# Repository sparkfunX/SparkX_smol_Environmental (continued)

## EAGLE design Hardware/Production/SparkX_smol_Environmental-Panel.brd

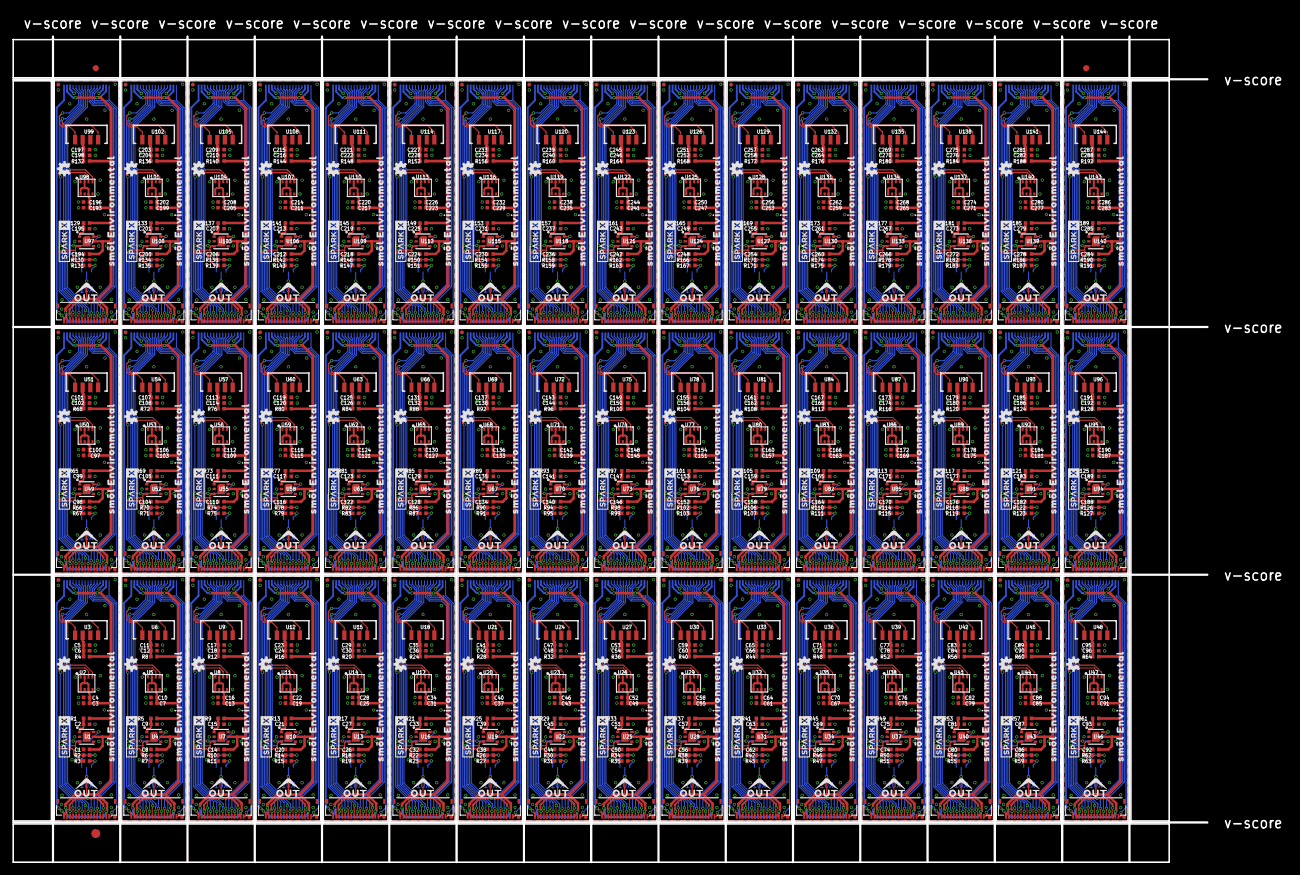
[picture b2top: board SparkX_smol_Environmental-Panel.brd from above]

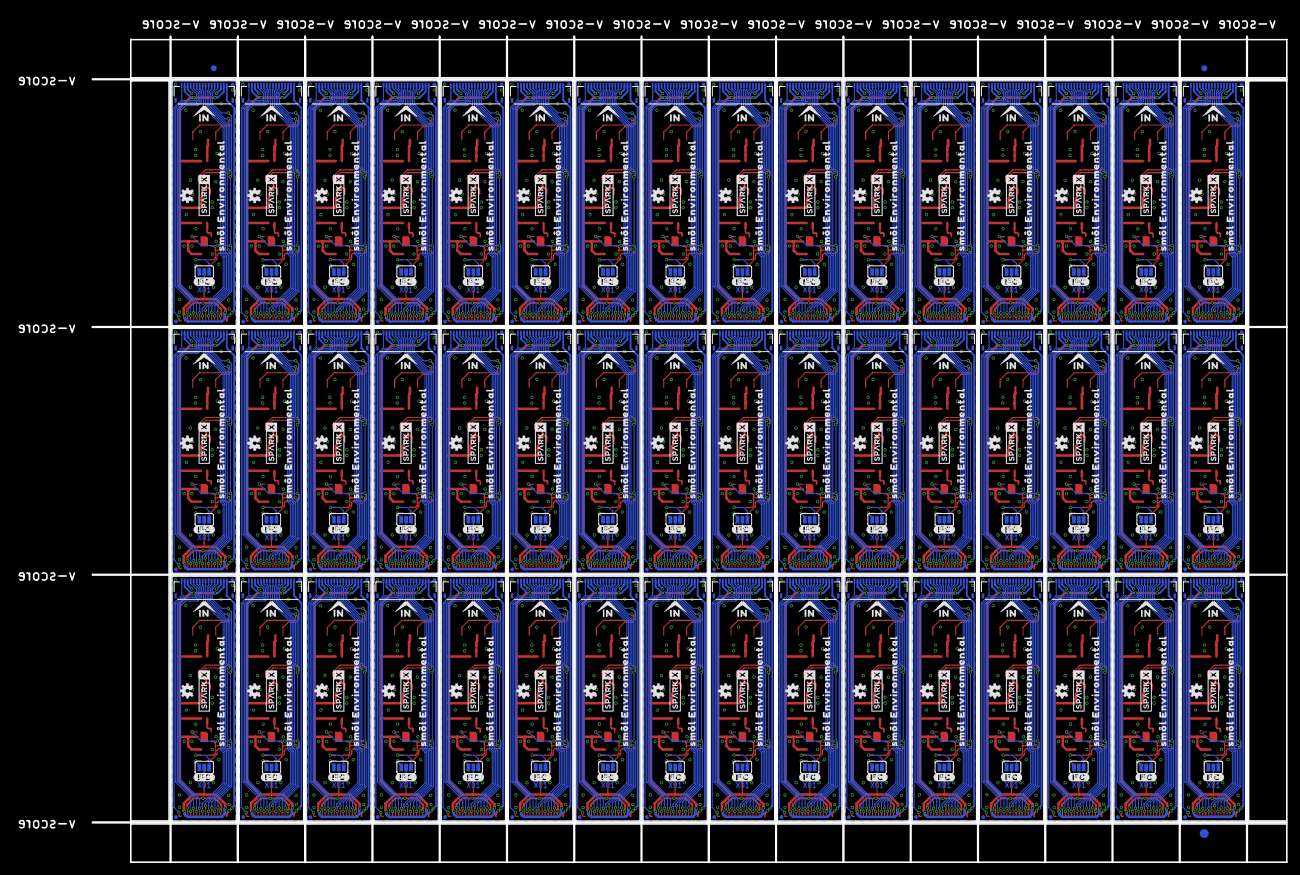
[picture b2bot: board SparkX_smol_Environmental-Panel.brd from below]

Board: 2 copper layers, 198.4 x 137.2 mm, 1494 parts (483 on the bottom side), 864 nets.

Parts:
C1, C2, C8, C9, C14, C15, C20, C21, C26, C27, C32, C33, C38, C39, C44, C45, C50, C51, C56, C57, C62, C63, C68, C69, C74, C75, C80, C81, C86, C87, C92, C93, C98, C99, C104, C105, C110, C111, C116, C117, C122, C123, C128, C129, C134, C135, C140, C141, C146, C147, C152, C153, C158, C159, C164, C165, C170, C171, C176, C177, C182, C183, C188, C189, C194, C195, C200, C201, C206, C207, C212, C213, C218, C219, C224, C225, C230, C231, C236, C237, C242, C243, C248, C249, C254, C255, C260, C261, C266, C267, C272, C273, C278, C279, C284, C285: 1.0uF; 0402-TIGHT
C3, C5, C7, C11, C13, C17, C19, C23, C25, C29, C31, C35, C37, C41, C43, C47, C49, C53, C55, C59, C61, C65, C67, C71, C73, C77, C79, C83, C85, C89, C91, C95, C97, C101, C103, C107, C109, C113, C115, C119, C121, C125, C127, C131, C133, C137, C139, C143, C145, C149, C151, C155, C157, C161, C163, C167, C169, C173, C175, C179, C181, C185, C187, C191, C193, C197, C199, C203, C205, C209, C211, C215, C217, C221, C223, C227, C229, C233, C235, C239, C241, C245, C247, C251, C253, C257, C259, C263, C265, C269, C271, C275, C277, C281, C283, C287: 2.2uF; 0402-TIGHT
C4, C6, C10, C12, C16, C18, C22, C24, C28, C30, C34, C36, C40, C42, C46, C48, C52, C54, C58, C60, C64, C66, C70, C72, C76, C78, C82, C84, C88, C90, C94, C96, C100, C102, C106, C108, C112, C114, C118, C120, C124, C126, C130, C132, C136, C138, C142, C144, C148, C150, C154, C156, C160, C162, C166, C168, C172, C174, C178, C180, C184, C186, C190, C192, C196, C198, C202, C204, C208, C210, C214, C216, C220, C222, C226, C228, C232, C234, C238, C240, C244, C246, C250, C252, C256, C258, C262, C264, C268, C270, C274, C276, C280, C282, C286, C288: 0.1uF; 0402-TIGHT
E$1, E$2, E$3, E$4: FIDUCIAL-1X2
E$5, E$6: FIDUCIAL-1.5X3
FD1, FD2, FD3, FD4, FD5, FD6, FD7, FD8, FD9, FD10, FD11, FD12, FD13, FD14, FD15, FD16, FD17, FD18, FD19, FD20, FD21, FD22, FD23, FD24, FD25, FD26, FD27, FD28, FD29, FD30, FD31, FD32, FD33, FD34, FD35, FD36, FD37, FD38, FD39, FD40, FD41, FD42, FD43, FD44, FD45, FD46, FD47, FD48, FD49, FD50, FD51, FD52, FD53, FD54, FD55, FD56, FD57, FD58, FD59, FD60, FD61, FD62, FD63, FD64, FD65, FD66, FD67, FD68, FD69, FD70, FD71, FD72, FD73, FD74, FD75, FD76, FD77, FD78, FD79, FD80, FD81, FD82, FD83, FD84, FD85, FD86, FD87, FD88, FD89, FD90, FD91, FD92, FD93, FD94, FD95, FD96, FD97, FD98, FD99, FD100, FD101, FD102, FD103, FD104, FD105, FD106, FD107, FD108, FD109, FD110, FD111, FD112, FD113, FD114, FD115, FD116, FD117, FD118, FD119, FD120, FD121, FD122, FD123, FD124, FD125, FD126, FD127, FD128, FD129, FD130, FD131, FD132, FD133, FD134, FD135, FD136, FD137, FD138, FD139, FD140, FD141, FD142, FD143, FD144, FD145, FD146, FD147, FD148, FD149, FD150, FD151, FD152, FD153, FD154, FD155, FD156, FD157, FD158, FD159, FD160, FD161, FD162, FD163, FD164, FD165, FD166, FD167, FD168, FD169, FD170, FD171, FD172, FD173, FD174, FD175, FD176, FD177, FD178, FD179, FD180, FD181, FD182, FD183, FD184, FD185, FD186, FD187, FD188, FD189, FD190, FD191, FD192: FIDUCIALUFIDUCIAL; FIDUCIAL-MICRO
IN, IN1, IN2, IN3, IN4, IN5, IN6, IN7, IN8, IN9, IN10, IN11, IN12, IN13, IN14, IN15, IN16, IN17, IN18, IN19, IN20, IN21, IN22, IN23, IN24, IN25, IN26, IN27, IN28, IN29, IN30, IN31, IN32, IN33, IN34, IN35, IN36, IN37, IN38, IN39, IN40, IN41, IN42, IN43, IN44, IN45, IN46, IN47: FPC_16_0.5MM
JP1, JP2, JP3, JP4, JP5, JP6, JP7, JP8, JP9, JP10, JP11, JP12, JP13, JP14, JP15, JP16, JP17, JP18, JP19, JP20, JP21, JP22, JP23, JP24, JP25, JP26, JP27, JP28, JP29, JP30, JP31, JP32, JP33, JP34, JP35, JP36, JP37, JP38, JP39, JP40, JP41, JP42, JP43, JP44, JP45, JP46, JP47, JP48: JUMPER-SMT_3_NO_SILK; SMT-JUMPER_3_NO_SILK
LOGO1, LOGO2, LOGO3, LOGO4, LOGO5, LOGO6, LOGO7, LOGO8, LOGO9, LOGO10, LOGO11, LOGO12, LOGO13, LOGO14, LOGO15, LOGO16, LOGO17, LOGO18, LOGO19, LOGO20, LOGO21, LOGO22, LOGO23, LOGO24, LOGO25, LOGO26, LOGO27, LOGO28, LOGO29, LOGO30, LOGO31, LOGO32, LOGO33, LOGO34, LOGO35, LOGO36, LOGO37, LOGO38, LOGO39, LOGO40, LOGO41, LOGO42, LOGO43, LOGO44, LOGO45, LOGO46, LOGO47, LOGO48, LOGO49, LOGO50, LOGO51, LOGO52, LOGO53, LOGO54, LOGO55, LOGO56, LOGO57, LOGO58, LOGO59, LOGO60, LOGO61, LOGO62, LOGO63, LOGO64, LOGO65, LOGO66, LOGO67, LOGO68, LOGO69, LOGO70, LOGO71, LOGO72, LOGO73, LOGO74, LOGO75, LOGO76, LOGO77, LOGO78, LOGO79, LOGO80, LOGO81, LOGO82, LOGO83, LOGO84, LOGO85, LOGO86, LOGO87, LOGO88, LOGO89, LOGO90, LOGO91, LOGO92, LOGO93, LOGO94, LOGO95, LOGO96: OSHW-LOGOMINI; OSHW-LOGO-MINI
OUT, OUT1, OUT2, OUT3, OUT4, OUT5, OUT6, OUT7, OUT8, OUT9, OUT10, OUT11, OUT12, OUT13, OUT14, OUT15, OUT16, OUT17, OUT18, OUT19, OUT20, OUT21, OUT22, OUT23, OUT24, OUT25, OUT26, OUT27, OUT28, OUT29, OUT30, OUT31, OUT32, OUT33, OUT34, OUT35, OUT36, OUT37, OUT38, OUT39, OUT40, OUT41, OUT42, OUT43, OUT44, OUT45, OUT46, OUT47: FPC_16_0.5MM
R1, R4, R5, R8, R9, R12, R13, R16, R17, R20, R21, R24, R25, R28, R29, R32, R33, R36, R37, R40, R41, R44, R45, R48, R49, R52, R53, R56, R57, R60, R61, R64, R65, R68, R69, R72, R73, R76, R77, R80, R81, R84, R85, R88, R89, R92, R93, R96, R97, R100, R101, R104, R105, R108, R109, R112, R113, R116, R117, R120, R121, R124, R125, R128, R129, R132, R133, R136, R137, R140, R141, R144, R145, R148, R149, R152, R153, R156, R157, R160, R161, R164, R165, R168, R169, R172, R173, R176, R177, R180, R181, R184, R185, R188, R189, R192: 4.7; 0402-TIGHT
R2, R3, R6, R7, R10, R11, R14, R15, R18, R19, R22, R23, R26, R27, R30, R31, R34, R35, R38, R39, R42, R43, R46, R47, R50, R51, R54, R55, R58, R59, R62, R63, R66, R67, R70, R71, R74, R75, R78, R79, R82, R83, R86, R87, R90, R91, R94, R95, R98, R99, R102, R103, R106, R107, R110, R111, R114, R115, R118, R119, R122, R123, R126, R127, R130, R131, R134, R135, R138, R139, R142, R143, R146, R147, R150, R151, R154, R155, R158, R159, R162, R163, R166, R167, R170, R171, R174, R175, R178, R179, R182, R183, R186, R187, R190, R191: 4.7k; 0402-TIGHT
U1, U4, U7, U10, U13, U16, U19, U22, U25, U28, U31, U34, U37, U40, U43, U46, U49, U52, U55, U58, U61, U64, U67, U70, U73, U76, U79, U82, U85, U88, U91, U94, U97, U100, U103, U106, U109, U112, U115, U118, U121, U124, U127, U130, U133, U136, U139, U142: SGP40
U2, U5, U8, U11, U14, U17, U20, U23, U26, U29, U32, U35, U38, U41, U44, U47, U50, U53, U56, U59, U62, U65, U68, U71, U74, U77, U80, U83, U86, U89, U92, U95, U98, U101, U104, U107, U110, U113, U116, U119, U122, U125, U128, U131, U134, U137, U140, U143: BME280; LGA-8-2.5X2.5
U3, U6, U9, U12, U15, U18, U21, U24, U27, U30, U33, U36, U39, U42, U45, U48, U51, U54, U57, U60, U63, U66, U69, U72, U75, U78, U81, U84, U87, U90, U93, U96, U99, U102, U105, U108, U111, U114, U117, U120, U123, U126, U129, U132, U135, U138, U141, U144: VEML7700-TT; VEML7700_TT
U$1, U$6, U$7, U$18, U$19, U$20, U$28, U$29, U$37, U$38, U$46, U$47, U$55, U$56, U$64, U$65, U$73, U$74, U$82, U$83, U$91, U$92, U$100, U$101, U$109, U$110, U$118, U$119, U$127, U$128, U$136, U$137, U$145, U$146, U$154, U$155, U$163, U$164, U$172, U$173, U$181, U$182, U$190, U$191, U$199, U$200, U$208, U$209, U$217, U$218, U$226, U$227, U$235, U$236, U$244, U$245, U$253, U$254, U$262, U$263, U$271, U$272, U$280, U$281, U$289, U$290, U$298, U$299, U$307, U$308, U$316, U$317, U$325, U$326, U$334, U$335, U$343, U$344, U$352, U$353, U$361, U$362, U$370, U$371, U$379, U$380, U$388, U$389, U$397, U$398, U$406, U$407, U$415, U$416, U$424, U$425: SPARKX-LOGO3; SPARKX-SMALL
U$2, U$4, U$14, U$15, U$25, U$26, U$34, U$35, U$43, U$44, U$52, U$53, U$61, U$62, U$70, U$71, U$79, U$80, U$88, U$89, U$97, U$98, U$106, U$107, U$115, U$116, U$124, U$125, U$133, U$134, U$142, U$143, U$151, U$152, U$160, U$161, U$169, U$170, U$178, U$179, U$187, U$188, U$196, U$197, U$205, U$206, U$214, U$215, U$223, U$224, U$232, U$233, U$241, U$242, U$250, U$251, U$259, U$260, U$268, U$269, U$277, U$278, U$286, U$287, U$295, U$296, U$304, U$305, U$313, U$314, U$322, U$323, U$331, U$332, U$340, U$341, U$349, U$350, U$358, U$359, U$367, U$368, U$376, U$377, U$385, U$386, U$394, U$395, U$403, U$404, U$412, U$413, U$421, U$422, U$430, U$431: SM�L_ENVIRONMENTAL0
U$3, U$9, U$12, U$13, U$23, U$24, U$32, U$33, U$41, U$42, U$50, U$51, U$59, U$60, U$68, U$69, U$77, U$78, U$86, U$87, U$95, U$96, U$104, U$105, U$113, U$114, U$122, U$123, U$131, U$132, U$140, U$141, U$149, U$150, U$158, U$159, U$167, U$168, U$176, U$177, U$185, U$186, U$194, U$195, U$203, U$204, U$212, U$213, U$221, U$222, U$230, U$231, U$239, U$240, U$248, U$249, U$257, U$258, U$266, U$267, U$275, U$276, U$284, U$285, U$293, U$294, U$302, U$303, U$311, U$312, U$320, U$321, U$329, U$330, U$338, U$339, U$347, U$348, U$356, U$357, U$365, U$366, U$374, U$375, U$383, U$384, U$392, U$393, U$401, U$402, U$410, U$411, U$419, U$420, U$428, U$429: SMOL_LOGOSMALL; SMOL_SMALL
U$5, U$16, U$27, U$36, U$45, U$54, U$63, U$72, U$81, U$90, U$99, U$108, U$117, U$126, U$135, U$144, U$153, U$162, U$171, U$180, U$189, U$198, U$207, U$216, U$225, U$234, U$243, U$252, U$261, U$270, U$279, U$288, U$297, U$306, U$315, U$324, U$333, U$342, U$351, U$360, U$369, U$378, U$387, U$396, U$405, U$414, U$423, U$432: #I�C#0
U$8, U$10, U$21, U$30, U$39, U$48, U$57, U$66, U$75, U$84, U$93, U$102, U$111, U$120, U$129, U$138, U$147, U$156, U$165, U$174, U$183, U$192, U$201, U$210, U$219, U$228, U$237, U$246, U$255, U$264, U$273, U$282, U$291, U$300, U$309, U$318, U$327, U$336, U$345, U$354, U$363, U$372, U$381, U$390, U$399, U$408, U$417, U$426: IN0
U$11, U$17, U$22, U$31, U$40, U$49, U$58, U$67, U$76, U$85, U$94, U$103, U$112, U$121, U$130, U$139, U$148, U$157, U$166, U$175, U$184, U$193, U$202, U$211, U$220, U$229, U$238, U$247, U$256, U$265, U$274, U$283, U$292, U$301, U$310, U$319, U$328, U$337, U$346, U$355, U$364, U$373, U$382, U$391, U$400, U$409, U$418, U$427: OUT0

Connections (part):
3.3V: C1.1, C3.1, C4.1, IN.2, IN.15, JP1.2, OUT.2, OUT.15, R1.2, R4.2, U1.5, U2.2, U2.6, U2.8
3.3V1: C7.1, C8.1, C10.1, IN1.2, IN1.15, JP2.2, OUT1.2, OUT1.15, R5.2, R8.2, U4.5, U5.2, U5.6, U5.8
3.3V2: C13.1, C14.1, C16.1, IN2.2, IN2.15, JP3.2, OUT2.2, OUT2.15, R9.2, R12.2, U7.5, U8.2, U8.6, U8.8
3.3V3: C19.1, C20.1, C22.1, IN3.2, IN3.15, JP4.2, OUT3.2, OUT3.15, R13.2, R16.2, U10.5, U11.2, U11.6, U11.8
3.3V4: C25.1, C26.1, C28.1, IN4.2, IN4.15, JP5.2, OUT4.2, OUT4.15, R17.2, R20.2, U13.5, U14.2, U14.6, U14.8
3.3V5: C31.1, C32.1, C34.1, IN5.2, IN5.15, JP6.2, OUT5.2, OUT5.15, R21.2, R24.2, U16.5, U17.2, U17.6, U17.8
3.3V6: C37.1, C38.1, C40.1, IN6.2, IN6.15, JP7.2, OUT6.2, OUT6.15, R25.2, R28.2, U19.5, U20.2, U20.6, U20.8
3.3V7: C43.1, C44.1, C46.1, IN7.2, IN7.15, JP8.2, OUT7.2, OUT7.15, R29.2, R32.2, U22.5, U23.2, U23.6, U23.8
3.3V8: C49.1, C50.1, C52.1, IN8.2, IN8.15, JP9.2, OUT8.2, OUT8.15, R33.2, R36.2, U25.5, U26.2, U26.6, U26.8
3.3V9: C55.1, C56.1, C58.1, IN9.2, IN9.15, JP10.2, OUT9.2, OUT9.15, R37.2, R40.2, U28.5, U29.2, U29.6, U29.8
3.3V10: C61.1, C62.1, C64.1, IN10.2, IN10.15, JP11.2, OUT10.2, OUT10.15, R41.2, R44.2, U31.5, U32.2, U32.6, U32.8
3.3V11: C67.1, C68.1, C70.1, IN11.2, IN11.15, JP12.2, OUT11.2, OUT11.15, R45.2, R48.2, U34.5, U35.2, U35.6, U35.8
3.3V12: C73.1, C74.1, C76.1, IN12.2, IN12.15, JP13.2, OUT12.2, OUT12.15, R49.2, R52.2, U37.5, U38.2, U38.6, U38.8
3.3V13: C79.1, C80.1, C82.1, IN13.2, IN13.15, JP14.2, OUT13.2, OUT13.15, R53.2, R56.2, U40.5, U41.2, U41.6, U41.8
3.3V14: C85.1, C86.1, C88.1, IN14.2, IN14.15, JP15.2, OUT14.2, OUT14.15, R57.2, R60.2, U43.5, U44.2, U44.6, U44.8
3.3V15: C91.1, C92.1, C94.1, IN15.2, IN15.15, JP16.2, OUT15.2, OUT15.15, R61.2, R64.2, U46.5, U47.2, U47.6, U47.8
3.3V16: C97.1, C98.1, C100.1, IN16.2, IN16.15, JP17.2, OUT16.2, OUT16.15, R65.2, R68.2, U49.5, U50.2, U50.6, U50.8
3.3V17: C103.1, C104.1, C106.1, IN17.2, IN17.15, JP18.2, OUT17.2, OUT17.15, R69.2, R72.2, U52.5, U53.2, U53.6, U53.8
3.3V18: C109.1, C110.1, C112.1, IN18.2, IN18.15, JP19.2, OUT18.2, OUT18.15, R73.2, R76.2, U55.5, U56.2, U56.6, U56.8
3.3V19: C115.1, C116.1, C118.1, IN19.2, IN19.15, JP20.2, OUT19.2, OUT19.15, R77.2, R80.2, U58.5, U59.2, U59.6, U59.8
3.3V20: C121.1, C122.1, C124.1, IN20.2, IN20.15, JP21.2, OUT20.2, OUT20.15, R81.2, R84.2, U61.5, U62.2, U62.6, U62.8
3.3V21: C127.1, C128.1, C130.1, IN21.2, IN21.15, JP22.2, OUT21.2, OUT21.15, R85.2, R88.2, U64.5, U65.2, U65.6, U65.8
3.3V22: C133.1, C134.1, C136.1, IN22.2, IN22.15, JP23.2, OUT22.2, OUT22.15, R89.2, R92.2, U67.5, U68.2, U68.6, U68.8
3.3V23: C139.1, C140.1, C142.1, IN23.2, IN23.15, JP24.2, OUT23.2, OUT23.15, R93.2, R96.2, U70.5, U71.2, U71.6, U71.8
3.3V24: C145.1, C146.1, C148.1, IN24.2, IN24.15, JP25.2, OUT24.2, OUT24.15, R97.2, R100.2, U73.5, U74.2, U74.6, U74.8
3.3V25: C151.1, C152.1, C154.1, IN25.2, IN25.15, JP26.2, OUT25.2, OUT25.15, R101.2, R104.2, U76.5, U77.2, U77.6, U77.8
3.3V26: C157.1, C158.1, C160.1, IN26.2, IN26.15, JP27.2, OUT26.2, OUT26.15, R105.2, R108.2, U79.5, U80.2, U80.6, U80.8
3.3V27: C163.1, C164.1, C166.1, IN27.2, IN27.15, JP28.2, OUT27.2, OUT27.15, R109.2, R112.2, U82.5, U83.2, U83.6, U83.8
3.3V28: C169.1, C170.1, C172.1, IN28.2, IN28.15, JP29.2, OUT28.2, OUT28.15, R113.2, R116.2, U85.5, U86.2, U86.6, U86.8
3.3V29: C175.1, C176.1, C178.1, IN29.2, IN29.15, JP30.2, OUT29.2, OUT29.15, R117.2, R120.2, U88.5, U89.2, U89.6, U89.8
3.3V30: C181.1, C182.1, C184.1, IN30.2, IN30.15, JP31.2, OUT30.2, OUT30.15, R121.2, R124.2, U91.5, U92.2, U92.6, U92.8
3.3V31: C187.1, C188.1, C190.1, IN31.2, IN31.15, JP32.2, OUT31.2, OUT31.15, R125.2, R128.2, U94.5, U95.2, U95.6, U95.8
3.3V32: C193.1, C194.1, C196.1, IN32.2, IN32.15, JP33.2, OUT32.2, OUT32.15, R129.2, R132.2, U97.5, U98.2, U98.6, U98.8
3.3V33: C199.1, C200.1, C202.1, IN33.2, IN33.15, JP34.2, OUT33.2, OUT33.15, R133.2, R136.2, U100.5, U101.2, U101.6, U101.8
3.3V34: C205.1, C206.1, C208.1, IN34.2, IN34.15, JP35.2, OUT34.2, OUT34.15, R137.2, R140.2, U103.5, U104.2, U104.6, U104.8
3.3V35: C211.1, C212.1, C214.1, IN35.2, IN35.15, JP36.2, OUT35.2, OUT35.15, R141.2, R144.2, U106.5, U107.2, U107.6, U107.8
3.3V36: C217.1, C218.1, C220.1, IN36.2, IN36.15, JP37.2, OUT36.2, OUT36.15, R145.2, R148.2, U109.5, U110.2, U110.6, U110.8
3.3V37: C223.1, C224.1, C226.1, IN37.2, IN37.15, JP38.2, OUT37.2, OUT37.15, R149.2, R152.2, U112.5, U113.2, U113.6, U113.8
3.3V38: C229.1, C230.1, C232.1, IN38.2, IN38.15, JP39.2, OUT38.2, OUT38.15, R153.2, R156.2, U115.5, U116.2, U116.6, U116.8
3.3V39: C235.1, C236.1, C238.1, IN39.2, IN39.15, JP40.2, OUT39.2, OUT39.15, R157.2, R160.2, U118.5, U119.2, U119.6, U119.8
3.3V40: C241.1, C242.1, C244.1, IN40.2, IN40.15, JP41.2, OUT40.2, OUT40.15, R161.2, R164.2, U121.5, U122.2, U122.6, U122.8
3.3V41: C247.1, C248.1, C250.1, IN41.2, IN41.15, JP42.2, OUT41.2, OUT41.15, R165.2, R168.2, U124.5, U125.2, U125.6, U125.8
3.3V42: C253.1, C254.1, C256.1, IN42.2, IN42.15, JP43.2, OUT42.2, OUT42.15, R169.2, R172.2, U127.5, U128.2, U128.6, U128.8
3.3V43: C259.1, C260.1, C262.1, IN43.2, IN43.15, JP44.2, OUT43.2, OUT43.15, R173.2, R176.2, U130.5, U131.2, U131.6, U131.8
3.3V44: C265.1, C266.1, C268.1, IN44.2, IN44.15, JP45.2, OUT44.2, OUT44.15, R177.2, R180.2, U133.5, U134.2, U134.6, U134.8
3.3V45: C271.1, C272.1, C274.1, IN45.2, IN45.15, JP46.2, OUT45.2, OUT45.15, R181.2, R184.2, U136.5, U137.2, U137.6, U137.8
3.3V46: C277.1, C278.1, C280.1, IN46.2, IN46.15, JP47.2, OUT46.2, OUT46.15, R185.2, R188.2, U139.5, U140.2, U140.6, U140.8
3.3V47: C283.1, C284.1, C286.1, IN47.2, IN47.15, JP48.2, OUT47.2, OUT47.15, R189.2, R192.2, U142.5, U143.2, U143.6, U143.8
CIPO: IN.6, OUT.6
CIPO1: IN1.6, OUT1.6
CIPO2: IN2.6, OUT2.6
CIPO3: IN3.6, OUT3.6
CIPO4: IN4.6, OUT4.6
CIPO5: IN5.6, OUT5.6
CIPO6: IN6.6, OUT6.6
CIPO7: IN7.6, OUT7.6
CIPO8: IN8.6, OUT8.6
CIPO9: IN9.6, OUT9.6
CIPO10: IN10.6, OUT10.6
CIPO11: IN11.6, OUT11.6
CIPO12: IN12.6, OUT12.6
CIPO13: IN13.6, OUT13.6
CIPO14: IN14.6, OUT14.6
CIPO15: IN15.6, OUT15.6
CIPO16: IN16.6, OUT16.6
CIPO17: IN17.6, OUT17.6
CIPO18: IN18.6, OUT18.6
CIPO19: IN19.6, OUT19.6
CIPO20: IN20.6, OUT20.6
CIPO21: IN21.6, OUT21.6
CIPO22: IN22.6, OUT22.6
CIPO23: IN23.6, OUT23.6
CIPO24: IN24.6, OUT24.6
CIPO25: IN25.6, OUT25.6
CIPO26: IN26.6, OUT26.6
CIPO27: IN27.6, OUT27.6
CIPO28: IN28.6, OUT28.6
CIPO29: IN29.6, OUT29.6
CIPO30: IN30.6, OUT30.6
CIPO31: IN31.6, OUT31.6
CIPO32: IN32.6, OUT32.6
CIPO33: IN33.6, OUT33.6
CIPO34: IN34.6, OUT34.6
CIPO35: IN35.6, OUT35.6
CIPO36: IN36.6, OUT36.6
CIPO37: IN37.6, OUT37.6
CIPO38: IN38.6, OUT38.6
CIPO39: IN39.6, OUT39.6
CIPO40: IN40.6, OUT40.6
CIPO41: IN41.6, OUT41.6
CIPO42: IN42.6, OUT42.6
CIPO43: IN43.6, OUT43.6
CIPO44: IN44.6, OUT44.6
CIPO45: IN45.6, OUT45.6
CIPO46: IN46.6, OUT46.6
CIPO47: IN47.6, OUT47.6
COPI: IN.5, OUT.5
COPI1: IN1.5, OUT1.5
COPI2: IN2.5, OUT2.5
COPI3: IN3.5, OUT3.5
COPI4: IN4.5, OUT4.5
COPI5: IN5.5, OUT5.5
COPI6: IN6.5, OUT6.5
COPI7: IN7.5, OUT7.5
COPI8: IN8.5, OUT8.5
COPI9: IN9.5, OUT9.5
COPI10: IN10.5, OUT10.5
COPI11: IN11.5, OUT11.5
COPI12: IN12.5, OUT12.5
COPI13: IN13.5, OUT13.5
COPI14: IN14.5, OUT14.5
COPI15: IN15.5, OUT15.5
COPI16: IN16.5, OUT16.5
COPI17: IN17.5, OUT17.5
COPI18: IN18.5, OUT18.5
COPI19: IN19.5, OUT19.5
COPI20: IN20.5, OUT20.5
COPI21: IN21.5, OUT21.5
COPI22: IN22.5, OUT22.5
COPI23: IN23.5, OUT23.5
COPI24: IN24.5, OUT24.5
COPI25: IN25.5, OUT25.5
COPI26: IN26.5, OUT26.5
COPI27: IN27.5, OUT27.5
COPI28: IN28.5, OUT28.5
COPI29: IN29.5, OUT29.5
COPI30: IN30.5, OUT30.5
COPI31: IN31.5, OUT31.5
COPI32: IN32.5, OUT32.5
COPI33: IN33.5, OUT33.5
COPI34: IN34.5, OUT34.5
COPI35: IN35.5, OUT35.5
COPI36: IN36.5, OUT36.5
COPI37: IN37.5, OUT37.5
COPI38: IN38.5, OUT38.5
COPI39: IN39.5, OUT39.5
COPI40: IN40.5, OUT40.5
COPI41: IN41.5, OUT41.5
COPI42: IN42.5, OUT42.5
COPI43: IN43.5, OUT43.5
COPI44: IN44.5, OUT44.5
COPI45: IN45.5, OUT45.5
COPI46: IN46.5, OUT46.5
COPI47: IN47.5, OUT47.5
CS0: IN.7, OUT.7
CS1: IN.8, OUT.8
CS2: IN.9, OUT.9
CS3: IN1.7, OUT1.7
CS4: IN1.8, OUT1.8
CS5: IN1.9, OUT1.9
CS6: IN2.7, OUT2.7
CS7: IN2.8, OUT2.8
CS8: IN2.9, OUT2.9
CS9: IN3.7, OUT3.7
CS10: IN3.8, OUT3.8
CS11: IN3.9, OUT3.9
CS12: IN4.7, OUT4.7
CS13: IN4.8, OUT4.8
CS14: IN4.9, OUT4.9
CS15: IN5.7, OUT5.7
CS16: IN5.8, OUT5.8
CS17: IN5.9, OUT5.9
CS18: IN6.7, OUT6.7
CS19: IN6.8, OUT6.8
CS20: IN6.9, OUT6.9
CS21: IN7.7, OUT7.7
CS22: IN7.8, OUT7.8
CS23: IN7.9, OUT7.9
CS24: IN8.7, OUT8.7
CS25: IN8.8, OUT8.8
CS26: IN8.9, OUT8.9
CS27: IN9.7, OUT9.7
CS28: IN9.8, OUT9.8
CS29: IN9.9, OUT9.9
CS30: IN10.7, OUT10.7
CS31: IN10.8, OUT10.8
CS32: IN10.9, OUT10.9
CS33: IN11.7, OUT11.7
CS34: IN11.8, OUT11.8
CS35: IN11.9, OUT11.9
CS36: IN12.7, OUT12.7
CS37: IN12.8, OUT12.8
CS38: IN12.9, OUT12.9
CS39: IN13.7, OUT13.7
CS40: IN13.8, OUT13.8
CS41: IN13.9, OUT13.9
CS42: IN14.7, OUT14.7
CS43: IN14.8, OUT14.8
CS44: IN14.9, OUT14.9
CS45: IN15.7, OUT15.7
CS46: IN15.8, OUT15.8
CS47: IN15.9, OUT15.9
CS48: IN16.7, OUT16.7
CS49: IN16.8, OUT16.8
CS50: IN16.9, OUT16.9
CS51: IN17.7, OUT17.7
CS52: IN17.8, OUT17.8
CS53: IN17.9, OUT17.9
CS54: IN18.7, OUT18.7
CS55: IN18.8, OUT18.8
CS56: IN18.9, OUT18.9
CS57: IN19.7, OUT19.7
CS58: IN19.8, OUT19.8
CS59: IN19.9, OUT19.9
CS60: IN20.7, OUT20.7
CS61: IN20.8, OUT20.8
CS62: IN20.9, OUT20.9
CS63: IN21.7, OUT21.7
CS64: IN21.8, OUT21.8
CS65: IN21.9, OUT21.9
CS66: IN22.7, OUT22.7
CS67: IN22.8, OUT22.8
CS68: IN22.9, OUT22.9
CS69: IN23.7, OUT23.7
CS70: IN23.8, OUT23.8
CS71: IN23.9, OUT23.9
CS72: IN24.7, OUT24.7
CS73: IN24.8, OUT24.8
CS74: IN24.9, OUT24.9
CS75: IN25.7, OUT25.7
CS76: IN25.8, OUT25.8
CS77: IN25.9, OUT25.9
CS78: IN26.7, OUT26.7
CS79: IN26.8, OUT26.8
CS80: IN26.9, OUT26.9
CS81: IN27.7, OUT27.7
CS82: IN27.8, OUT27.8
CS83: IN27.9, OUT27.9
CS84: IN28.7, OUT28.7
CS85: IN28.8, OUT28.8
CS86: IN28.9, OUT28.9
CS87: IN29.7, OUT29.7
CS88: IN29.8, OUT29.8
CS89: IN29.9, OUT29.9
CS90: IN30.7, OUT30.7
CS91: IN30.8, OUT30.8
CS92: IN30.9, OUT30.9
CS93: IN31.7, OUT31.7
CS94: IN31.8, OUT31.8
CS95: IN31.9, OUT31.9
CS96: IN32.7, OUT32.7
CS97: IN32.8, OUT32.8
CS98: IN32.9, OUT32.9
CS99: IN33.7, OUT33.7
CS100: IN33.8, OUT33.8
CS101: IN33.9, OUT33.9
CS102: IN34.7, OUT34.7
CS103: IN34.8, OUT34.8
CS104: IN34.9, OUT34.9
CS105: IN35.7, OUT35.7
CS106: IN35.8, OUT35.8
CS107: IN35.9, OUT35.9
CS108: IN36.7, OUT36.7
CS109: IN36.8, OUT36.8
CS110: IN36.9, OUT36.9
CS111: IN37.7, OUT37.7
CS112: IN37.8, OUT37.8
CS113: IN37.9, OUT37.9
CS114: IN38.7, OUT38.7
CS115: IN38.8, OUT38.8
CS116: IN38.9, OUT38.9
CS117: IN39.7, OUT39.7
CS118: IN39.8, OUT39.8
CS119: IN39.9, OUT39.9
CS120: IN40.7, OUT40.7
CS121: IN40.8, OUT40.8
CS122: IN40.9, OUT40.9
CS123: IN41.7, OUT41.7
CS124: IN41.8, OUT41.8
CS125: IN41.9, OUT41.9
CS126: IN42.7, OUT42.7
CS127: IN42.8, OUT42.8
CS128: IN42.9, OUT42.9
CS129: IN43.7, OUT43.7
CS130: IN43.8, OUT43.8
CS131: IN43.9, OUT43.9
CS132: IN44.7, OUT44.7
CS133: IN44.8, OUT44.8
CS134: IN44.9, OUT44.9
CS135: IN45.7, OUT45.7
CS136: IN45.8, OUT45.8
CS137: IN45.9, OUT45.9
CS138: IN46.7, OUT46.7
CS139: IN46.8, OUT46.8
CS140: IN46.9, OUT46.9
CS141: IN47.7, OUT47.7
CS142: IN47.8, OUT47.8
CS143: IN47.9, OUT47.9
GND: C1.2, C2.2, C3.2, C4.2, C5.2, C6.2, IN.3, IN.14, OUT.3, OUT.14, U1.2, U1.4, U1.DIEPAD, U2.1, U2.5, U2.7, U3.3
GND1: C7.2, C8.2, C9.2, C10.2, C11.2, C12.2, IN1.3, IN1.14, OUT1.3, OUT1.14, U4.2, U4.4, U4.DIEPAD, U5.1, U5.5, U5.7, U6.3
GND2: C13.2, C14.2, C15.2, C16.2, C17.2, C18.2, IN2.3, IN2.14, OUT2.3, OUT2.14, U7.2, U7.4, U7.DIEPAD, U8.1, U8.5, U8.7, U9.3
GND3: C19.2, C20.2, C21.2, C22.2, C23.2, C24.2, IN3.3, IN3.14, OUT3.3, OUT3.14, U10.2, U10.4, U10.DIEPAD, U11.1, U11.5, U11.7, U12.3
GND4: C25.2, C26.2, C27.2, C28.2, C29.2, C30.2, IN4.3, IN4.14, OUT4.3, OUT4.14, U13.2, U13.4, U13.DIEPAD, U14.1, U14.5, U14.7, U15.3
GND5: C31.2, C32.2, C33.2, C34.2, C35.2, C36.2, IN5.3, IN5.14, OUT5.3, OUT5.14, U16.2, U16.4, U16.DIEPAD, U17.1, U17.5, U17.7, U18.3
GND6: C37.2, C38.2, C39.2, C40.2, C41.2, C42.2, IN6.3, IN6.14, OUT6.3, OUT6.14, U19.2, U19.4, U19.DIEPAD, U20.1, U20.5, U20.7, U21.3
GND7: C43.2, C44.2, C45.2, C46.2, C47.2, C48.2, IN7.3, IN7.14, OUT7.3, OUT7.14, U22.2, U22.4, U22.DIEPAD, U23.1, U23.5, U23.7, U24.3
GND8: C49.2, C50.2, C51.2, C52.2, C53.2, C54.2, IN8.3, IN8.14, OUT8.3, OUT8.14, U25.2, U25.4, U25.DIEPAD, U26.1, U26.5, U26.7, U27.3
GND9: C55.2, C56.2, C57.2, C58.2, C59.2, C60.2, IN9.3, IN9.14, OUT9.3, OUT9.14, U28.2, U28.4, U28.DIEPAD, U29.1, U29.5, U29.7, U30.3
GND10: C61.2, C62.2, C63.2, C64.2, C65.2, C66.2, IN10.3, IN10.14, OUT10.3, OUT10.14, U31.2, U31.4, U31.DIEPAD, U32.1, U32.5, U32.7, U33.3
GND11: C67.2, C68.2, C69.2, C70.2, C71.2, C72.2, IN11.3, IN11.14, OUT11.3, OUT11.14, U34.2, U34.4, U34.DIEPAD, U35.1, U35.5, U35.7, U36.3
GND12: C73.2, C74.2, C75.2, C76.2, C77.2, C78.2, IN12.3, IN12.14, OUT12.3, OUT12.14, U37.2, U37.4, U37.DIEPAD, U38.1, U38.5, U38.7, U39.3
GND13: C79.2, C80.2, C81.2, C82.2, C83.2, C84.2, IN13.3, IN13.14, OUT13.3, OUT13.14, U40.2, U40.4, U40.DIEPAD, U41.1, U41.5, U41.7, U42.3
GND14: C85.2, C86.2, C87.2, C88.2, C89.2, C90.2, IN14.3, IN14.14, OUT14.3, OUT14.14, U43.2, U43.4, U43.DIEPAD, U44.1, U44.5, U44.7, U45.3
GND15: C91.2, C92.2, C93.2, C94.2, C95.2, C96.2, IN15.3, IN15.14, OUT15.3, OUT15.14, U46.2, U46.4, U46.DIEPAD, U47.1, U47.5, U47.7, U48.3
GND16: C97.2, C98.2, C99.2, C100.2, C101.2, C102.2, IN16.3, IN16.14, OUT16.3, OUT16.14, U49.2, U49.4, U49.DIEPAD, U50.1, U50.5, U50.7, U51.3
GND17: C103.2, C104.2, C105.2, C106.2, C107.2, C108.2, IN17.3, IN17.14, OUT17.3, OUT17.14, U52.2, U52.4, U52.DIEPAD, U53.1, U53.5, U53.7, U54.3
GND18: C109.2, C110.2, C111.2, C112.2, C113.2, C114.2, IN18.3, IN18.14, OUT18.3, OUT18.14, U55.2, U55.4, U55.DIEPAD, U56.1, U56.5, U56.7, U57.3
GND19: C115.2, C116.2, C117.2, C118.2, C119.2, C120.2, IN19.3, IN19.14, OUT19.3, OUT19.14, U58.2, U58.4, U58.DIEPAD, U59.1, U59.5, U59.7, U60.3
GND20: C121.2, C122.2, C123.2, C124.2, C125.2, C126.2, IN20.3, IN20.14, OUT20.3, OUT20.14, U61.2, U61.4, U61.DIEPAD, U62.1, U62.5, U62.7, U63.3
GND21: C127.2, C128.2, C129.2, C130.2, C131.2, C132.2, IN21.3, IN21.14, OUT21.3, OUT21.14, U64.2, U64.4, U64.DIEPAD, U65.1, U65.5, U65.7, U66.3
GND22: C133.2, C134.2, C135.2, C136.2, C137.2, C138.2, IN22.3, IN22.14, OUT22.3, OUT22.14, U67.2, U67.4, U67.DIEPAD, U68.1, U68.5, U68.7, U69.3
GND23: C139.2, C140.2, C141.2, C142.2, C143.2, C144.2, IN23.3, IN23.14, OUT23.3, OUT23.14, U70.2, U70.4, U70.DIEPAD, U71.1, U71.5, U71.7, U72.3
GND24: C145.2, C146.2, C147.2, C148.2, C149.2, C150.2, IN24.3, IN24.14, OUT24.3, OUT24.14, U73.2, U73.4, U73.DIEPAD, U74.1, U74.5, U74.7, U75.3
GND25: C151.2, C152.2, C153.2, C154.2, C155.2, C156.2, IN25.3, IN25.14, OUT25.3, OUT25.14, U76.2, U76.4, U76.DIEPAD, U77.1, U77.5, U77.7, U78.3
GND26: C157.2, C158.2, C159.2, C160.2, C161.2, C162.2, IN26.3, IN26.14, OUT26.3, OUT26.14, U79.2, U79.4, U79.DIEPAD, U80.1, U80.5, U80.7, U81.3
GND27: C163.2, C164.2, C165.2, C166.2, C167.2, C168.2, IN27.3, IN27.14, OUT27.3, OUT27.14, U82.2, U82.4, U82.DIEPAD, U83.1, U83.5, U83.7, U84.3
GND28: C169.2, C170.2, C171.2, C172.2, C173.2, C174.2, IN28.3, IN28.14, OUT28.3, OUT28.14, U85.2, U85.4, U85.DIEPAD, U86.1, U86.5, U86.7, U87.3
GND29: C175.2, C176.2, C177.2, C178.2, C179.2, C180.2, IN29.3, IN29.14, OUT29.3, OUT29.14, U88.2, U88.4, U88.DIEPAD, U89.1, U89.5, U89.7, U90.3
GND30: C181.2, C182.2, C183.2, C184.2, C185.2, C186.2, IN30.3, IN30.14, OUT30.3, OUT30.14, U91.2, U91.4, U91.DIEPAD, U92.1, U92.5, U92.7, U93.3
GND31: C187.2, C188.2, C189.2, C190.2, C191.2, C192.2, IN31.3, IN31.14, OUT31.3, OUT31.14, U94.2, U94.4, U94.DIEPAD, U95.1, U95.5, U95.7, U96.3
GND32: C193.2, C194.2, C195.2, C196.2, C197.2, C198.2, IN32.3, IN32.14, OUT32.3, OUT32.14, U97.2, U97.4, U97.DIEPAD, U98.1, U98.5, U98.7, U99.3
GND33: C199.2, C200.2, C201.2, C202.2, C203.2, C204.2, IN33.3, IN33.14, OUT33.3, OUT33.14, U100.2, U100.4, U100.DIEPAD, U101.1, U101.5, U101.7, U102.3
GND34: C205.2, C206.2, C207.2, C208.2, C209.2, C210.2, IN34.3, IN34.14, OUT34.3, OUT34.14, U103.2, U103.4, U103.DIEPAD, U104.1, U104.5, U104.7, U105.3
GND35: C211.2, C212.2, C213.2, C214.2, C215.2, C216.2, IN35.3, IN35.14, OUT35.3, OUT35.14, U106.2, U106.4, U106.DIEPAD, U107.1, U107.5, U107.7, U108.3
GND36: C217.2, C218.2, C219.2, C220.2, C221.2, C222.2, IN36.3, IN36.14, OUT36.3, OUT36.14, U109.2, U109.4, U109.DIEPAD, U110.1, U110.5, U110.7, U111.3
GND37: C223.2, C224.2, C225.2, C226.2, C227.2, C228.2, IN37.3, IN37.14, OUT37.3, OUT37.14, U112.2, U112.4, U112.DIEPAD, U113.1, U113.5, U113.7, U114.3
GND38: C229.2, C230.2, C231.2, C232.2, C233.2, C234.2, IN38.3, IN38.14, OUT38.3, OUT38.14, U115.2, U115.4, U115.DIEPAD, U116.1, U116.5, U116.7, U117.3
GND39: C235.2, C236.2, C237.2, C238.2, C239.2, C240.2, IN39.3, IN39.14, OUT39.3, OUT39.14, U118.2, U118.4, U118.DIEPAD, U119.1, U119.5, U119.7, U120.3
GND40: C241.2, C242.2, C243.2, C244.2, C245.2, C246.2, IN40.3, IN40.14, OUT40.3, OUT40.14, U121.2, U121.4, U121.DIEPAD, U122.1, U122.5, U122.7, U123.3
GND41: C247.2, C248.2, C249.2, C250.2, C251.2, C252.2, IN41.3, IN41.14, OUT41.3, OUT41.14, U124.2, U124.4, U124.DIEPAD, U125.1, U125.5, U125.7, U126.3
GND42: C253.2, C254.2, C255.2, C256.2, C257.2, C258.2, IN42.3, IN42.14, OUT42.3, OUT42.14, U127.2, U127.4, U127.DIEPAD, U128.1, U128.5, U128.7, U129.3
GND43: C259.2, C260.2, C261.2, C262.2, C263.2, C264.2, IN43.3, IN43.14, OUT43.3, OUT43.14, U130.2, U130.4, U130.DIEPAD, U131.1, U131.5, U131.7, U132.3
GND44: C265.2, C266.2, C267.2, C268.2, C269.2, C270.2, IN44.3, IN44.14, OUT44.3, OUT44.14, U133.2, U133.4, U133.DIEPAD, U134.1, U134.5, U134.7, U135.3
GND45: C271.2, C272.2, C273.2, C274.2, C275.2, C276.2, IN45.3, IN45.14, OUT45.3, OUT45.14, U136.2, U136.4, U136.DIEPAD, U137.1, U137.5, U137.7, U138.3
GND46: C277.2, C278.2, C279.2, C280.2, C281.2, C282.2, IN46.3, IN46.14, OUT46.3, OUT46.14, U139.2, U139.4, U139.DIEPAD, U140.1, U140.5, U140.7, U141.3
GND47: C283.2, C284.2, C285.2, C286.2, C287.2, C288.2, IN47.3, IN47.14, OUT47.3, OUT47.14, U142.2, U142.4, U142.DIEPAD, U143.1, U143.5, U143.7, U144.3
GPIO0: IN.10, OUT.10
GPIO1: IN.11, OUT.11
GPIO2: IN1.10, OUT1.10
GPIO3: IN1.11, OUT1.11
GPIO4: IN2.10, OUT2.10
GPIO5: IN2.11, OUT2.11
GPIO6: IN3.10, OUT3.10
GPIO7: IN3.11, OUT3.11
GPIO8: IN4.10, OUT4.10
GPIO9: IN4.11, OUT4.11
GPIO10: IN5.10, OUT5.10
GPIO11: IN5.11, OUT5.11
GPIO12: IN6.10, OUT6.10
GPIO13: IN6.11, OUT6.11
GPIO14: IN7.10, OUT7.10
GPIO15: IN7.11, OUT7.11
GPIO16: IN8.10, OUT8.10
GPIO17: IN8.11, OUT8.11
GPIO18: IN9.10, OUT9.10
GPIO19: IN9.11, OUT9.11
GPIO20: IN10.10, OUT10.10
GPIO21: IN10.11, OUT10.11
GPIO22: IN11.10, OUT11.10
GPIO23: IN11.11, OUT11.11
GPIO24: IN12.10, OUT12.10
GPIO25: IN12.11, OUT12.11
GPIO26: IN13.10, OUT13.10
GPIO27: IN13.11, OUT13.11
GPIO28: IN14.10, OUT14.10
GPIO29: IN14.11, OUT14.11
GPIO30: IN15.10, OUT15.10
GPIO31: IN15.11, OUT15.11
GPIO32: IN16.10, OUT16.10
GPIO33: IN16.11, OUT16.11
GPIO34: IN17.10, OUT17.10
GPIO35: IN17.11, OUT17.11
GPIO36: IN18.10, OUT18.10
GPIO37: IN18.11, OUT18.11
GPIO38: IN19.10, OUT19.10
GPIO39: IN19.11, OUT19.11
GPIO40: IN20.10, OUT20.10
GPIO41: IN20.11, OUT20.11
GPIO42: IN21.10, OUT21.10
GPIO43: IN21.11, OUT21.11
GPIO44: IN22.10, OUT22.10
GPIO45: IN22.11, OUT22.11
GPIO46: IN23.10, OUT23.10
GPIO47: IN23.11, OUT23.11
GPIO48: IN24.10, OUT24.10
GPIO49: IN24.11, OUT24.11
GPIO50: IN25.10, OUT25.10
GPIO51: IN25.11, OUT25.11
GPIO52: IN26.10, OUT26.10
GPIO53: IN26.11, OUT26.11
GPIO54: IN27.10, OUT27.10
GPIO55: IN27.11, OUT27.11
GPIO56: IN28.10, OUT28.10
GPIO57: IN28.11, OUT28.11
GPIO58: IN29.10, OUT29.10
GPIO59: IN29.11, OUT29.11
GPIO60: IN30.10, OUT30.10
GPIO61: IN30.11, OUT30.11
GPIO62: IN31.10, OUT31.10
GPIO63: IN31.11, OUT31.11
GPIO64: IN32.10, OUT32.10
GPIO65: IN32.11, OUT32.11
GPIO66: IN33.10, OUT33.10
GPIO67: IN33.11, OUT33.11
GPIO68: IN34.10, OUT34.10
GPIO69: IN34.11, OUT34.11
GPIO70: IN35.10, OUT35.10
GPIO71: IN35.11, OUT35.11
GPIO72: IN36.10, OUT36.10
GPIO73: IN36.11, OUT36.11
GPIO74: IN37.10, OUT37.10
GPIO75: IN37.11, OUT37.11
GPIO76: IN38.10, OUT38.10
GPIO77: IN38.11, OUT38.11
GPIO78: IN39.10, OUT39.10
GPIO79: IN39.11, OUT39.11
GPIO80: IN40.10, OUT40.10
GPIO81: IN40.11, OUT40.11
GPIO82: IN41.10, OUT41.10
GPIO83: IN41.11, OUT41.11
GPIO84: IN42.10, OUT42.10
GPIO85: IN42.11, OUT42.11
GPIO86: IN43.10, OUT43.10
GPIO87: IN43.11, OUT43.11
GPIO88: IN44.10, OUT44.10
GPIO89: IN44.11, OUT44.11
GPIO90: IN45.10, OUT45.10
GPIO91: IN45.11, OUT45.11
GPIO92: IN46.10, OUT46.10
GPIO93: IN46.11, OUT46.11
GPIO94: IN47.10, OUT47.10
GPIO95: IN47.11, OUT47.11
unnamed: C2.1, R1.1, U1.1
unnamed: JP1.3, R2.2
unnamed: JP1.1, R3.2
unnamed: C5.1, C6.1, R4.1, U3.2
unnamed: C9.1, R5.1, U4.1
unnamed: JP2.3, R6.2
unnamed: JP2.1, R7.2
unnamed: C11.1, C12.1, R8.1, U6.2
unnamed: C15.1, R9.1, U7.1
unnamed: JP3.3, R10.2
unnamed: JP3.1, R11.2
unnamed: C17.1, C18.1, R12.1, U9.2
unnamed: C21.1, R13.1, U10.1
unnamed: JP4.3, R14.2
unnamed: JP4.1, R15.2
unnamed: C23.1, C24.1, R16.1, U12.2
unnamed: C27.1, R17.1, U13.1
unnamed: JP5.3, R18.2
unnamed: JP5.1, R19.2
unnamed: C29.1, C30.1, R20.1, U15.2
unnamed: C33.1, R21.1, U16.1
unnamed: JP6.3, R22.2
unnamed: JP6.1, R23.2
unnamed: C35.1, C36.1, R24.1, U18.2
unnamed: C39.1, R25.1, U19.1
unnamed: JP7.3, R26.2
unnamed: JP7.1, R27.2
unnamed: C41.1, C42.1, R28.1, U21.2
unnamed: C45.1, R29.1, U22.1
unnamed: JP8.3, R30.2
unnamed: JP8.1, R31.2
unnamed: C47.1, C48.1, R32.1, U24.2
unnamed: C51.1, R33.1, U25.1
unnamed: JP9.3, R34.2
unnamed: JP9.1, R35.2
unnamed: C53.1, C54.1, R36.1, U27.2
unnamed: C57.1, R37.1, U28.1
unnamed: JP10.3, R38.2
unnamed: JP10.1, R39.2
unnamed: C59.1, C60.1, R40.1, U30.2
unnamed: C63.1, R41.1, U31.1
unnamed: JP11.3, R42.2
unnamed: JP11.1, R43.2
unnamed: C65.1, C66.1, R44.1, U33.2
unnamed: C69.1, R45.1, U34.1
unnamed: JP12.3, R46.2
unnamed: JP12.1, R47.2
unnamed: C71.1, C72.1, R48.1, U36.2
unnamed: C75.1, R49.1, U37.1
unnamed: JP13.3, R50.2
unnamed: JP13.1, R51.2
unnamed: C77.1, C78.1, R52.1, U39.2
unnamed: C81.1, R53.1, U40.1
unnamed: JP14.3, R54.2
unnamed: JP14.1, R55.2
unnamed: C83.1, C84.1, R56.1, U42.2
unnamed: C87.1, R57.1, U43.1
unnamed: JP15.3, R58.2
unnamed: JP15.1, R59.2
unnamed: C89.1, C90.1, R60.1, U45.2
unnamed: C93.1, R61.1, U46.1
unnamed: JP16.3, R62.2
unnamed: JP16.1, R63.2
unnamed: C95.1, C96.1, R64.1, U48.2
unnamed: C99.1, R65.1, U49.1
unnamed: JP17.3, R66.2
unnamed: JP17.1, R67.2
unnamed: C101.1, C102.1, R68.1, U51.2
unnamed: C105.1, R69.1, U52.1
unnamed: JP18.3, R70.2
unnamed: JP18.1, R71.2
unnamed: C107.1, C108.1, R72.1, U54.2
unnamed: C111.1, R73.1, U55.1
unnamed: JP19.3, R74.2
unnamed: JP19.1, R75.2
unnamed: C113.1, C114.1, R76.1, U57.2
unnamed: C117.1, R77.1, U58.1
unnamed: JP20.3, R78.2
unnamed: JP20.1, R79.2
unnamed: C119.1, C120.1, R80.1, U60.2
unnamed: C123.1, R81.1, U61.1
unnamed: JP21.3, R82.2
unnamed: JP21.1, R83.2
unnamed: C125.1, C126.1, R84.1, U63.2
unnamed: C129.1, R85.1, U64.1
unnamed: JP22.3, R86.2
unnamed: JP22.1, R87.2
unnamed: C131.1, C132.1, R88.1, U66.2
unnamed: C135.1, R89.1, U67.1
unnamed: JP23.3, R90.2
unnamed: JP23.1, R91.2
unnamed: C137.1, C138.1, R92.1, U69.2
unnamed: C141.1, R93.1, U70.1
unnamed: JP24.3, R94.2
unnamed: JP24.1, R95.2
unnamed: C143.1, C144.1, R96.1, U72.2
unnamed: C147.1, R97.1, U73.1
unnamed: JP25.3, R98.2
unnamed: JP25.1, R99.2
unnamed: C149.1, C150.1, R100.1, U75.2
unnamed: C153.1, R101.1, U76.1
unnamed: JP26.3, R102.2
unnamed: JP26.1, R103.2
unnamed: C155.1, C156.1, R104.1, U78.2
unnamed: C159.1, R105.1, U79.1
unnamed: JP27.3, R106.2
unnamed: JP27.1, R107.2
unnamed: C161.1, C162.1, R108.1, U81.2
unnamed: C165.1, R109.1, U82.1
unnamed: JP28.3, R110.2
unnamed: JP28.1, R111.2
unnamed: C167.1, C168.1, R112.1, U84.2
unnamed: C171.1, R113.1, U85.1
unnamed: JP29.3, R114.2
unnamed: JP29.1, R115.2
unnamed: C173.1, C174.1, R116.1, U87.2
unnamed: C177.1, R117.1, U88.1
unnamed: JP30.3, R118.2
unnamed: JP30.1, R119.2
unnamed: C179.1, C180.1, R120.1, U90.2
unnamed: C183.1, R121.1, U91.1
unnamed: JP31.3, R122.2
unnamed: JP31.1, R123.2
unnamed: C185.1, C186.1, R124.1, U93.2
unnamed: C189.1, R125.1, U94.1
unnamed: JP32.3, R126.2
unnamed: JP32.1, R127.2
unnamed: C191.1, C192.1, R128.1, U96.2
unnamed: C195.1, R129.1, U97.1
unnamed: JP33.3, R130.2
unnamed: JP33.1, R131.2
unnamed: C197.1, C198.1, R132.1, U99.2
unnamed: C201.1, R133.1, U100.1
unnamed: JP34.3, R134.2
unnamed: JP34.1, R135.2
unnamed: C203.1, C204.1, R136.1, U102.2
unnamed: C207.1, R137.1, U103.1
unnamed: JP35.3, R138.2
unnamed: JP35.1, R139.2
unnamed: C209.1, C210.1, R140.1, U105.2
unnamed: C213.1, R141.1, U106.1
unnamed: JP36.3, R142.2
unnamed: JP36.1, R143.2
unnamed: C215.1, C216.1, R144.1, U108.2
unnamed: C219.1, R145.1, U109.1
unnamed: JP37.3, R146.2
unnamed: JP37.1, R147.2
unnamed: C221.1, C222.1, R148.1, U111.2
unnamed: C225.1, R149.1, U112.1
unnamed: JP38.3, R150.2
unnamed: JP38.1, R151.2
unnamed: C227.1, C228.1, R152.1, U114.2
unnamed: C231.1, R153.1, U115.1
unnamed: JP39.3, R154.2
unnamed: JP39.1, R155.2
unnamed: C233.1, C234.1, R156.1, U117.2
unnamed: C237.1, R157.1, U118.1
unnamed: JP40.3, R158.2
unnamed: JP40.1, R159.2
unnamed: C239.1, C240.1, R160.1, U120.2
unnamed: C243.1, R161.1, U121.1
unnamed: JP41.3, R162.2
unnamed: JP41.1, R163.2
unnamed: C245.1, C246.1, R164.1, U123.2
unnamed: C249.1, R165.1, U124.1
unnamed: JP42.3, R166.2
unnamed: JP42.1, R167.2
unnamed: C251.1, C252.1, R168.1, U126.2
unnamed: C255.1, R169.1, U127.1
unnamed: JP43.3, R170.2
unnamed: JP43.1, R171.2
unnamed: C257.1, C258.1, R172.1, U129.2
unnamed: C261.1, R173.1, U130.1
unnamed: JP44.3, R174.2
unnamed: JP44.1, R175.2
unnamed: C263.1, C264.1, R176.1, U132.2
unnamed: C267.1, R177.1, U133.1
unnamed: JP45.3, R178.2
unnamed: JP45.1, R179.2
unnamed: C269.1, C270.1, R180.1, U135.2
unnamed: C273.1, R181.1, U136.1
unnamed: JP46.3, R182.2
unnamed: JP46.1, R183.2
unnamed: C275.1, C276.1, R184.1, U138.2
unnamed: C279.1, R185.1, U139.1
unnamed: JP47.3, R186.2
unnamed: JP47.1, R187.2
unnamed: C281.1, C282.1, R188.1, U141.2
unnamed: C285.1, R189.1, U142.1
unnamed: JP48.3, R190.2
unnamed: JP48.1, R191.2
unnamed: C287.1, C288.1, R192.1, U144.2
PROC_PWR_EN: IN.1, OUT.1
PROC_PWR_EN1: IN1.1, OUT1.1
PROC_PWR_EN2: IN2.1, OUT2.1
PROC_PWR_EN3: IN3.1, OUT3.1
PROC_PWR_EN4: IN4.1, OUT4.1
PROC_PWR_EN5: IN5.1, OUT5.1
PROC_PWR_EN6: IN6.1, OUT6.1
PROC_PWR_EN7: IN7.1, OUT7.1
PROC_PWR_EN8: IN8.1, OUT8.1
PROC_PWR_EN9: IN9.1, OUT9.1
PROC_PWR_EN10: IN10.1, OUT10.1
PROC_PWR_EN11: IN11.1, OUT11.1
PROC_PWR_EN12: IN12.1, OUT12.1
PROC_PWR_EN13: IN13.1, OUT13.1
PROC_PWR_EN14: IN14.1, OUT14.1
PROC_PWR_EN15: IN15.1, OUT15.1
PROC_PWR_EN16: IN16.1, OUT16.1
PROC_PWR_EN17: IN17.1, OUT17.1
PROC_PWR_EN18: IN18.1, OUT18.1
PROC_PWR_EN19: IN19.1, OUT19.1
PROC_PWR_EN20: IN20.1, OUT20.1
PROC_PWR_EN21: IN21.1, OUT21.1
PROC_PWR_EN22: IN22.1, OUT22.1
PROC_PWR_EN23: IN23.1, OUT23.1
PROC_PWR_EN24: IN24.1, OUT24.1
PROC_PWR_EN25: IN25.1, OUT25.1
PROC_PWR_EN26: IN26.1, OUT26.1
PROC_PWR_EN27: IN27.1, OUT27.1
PROC_PWR_EN28: IN28.1, OUT28.1
PROC_PWR_EN29: IN29.1, OUT29.1
PROC_PWR_EN30: IN30.1, OUT30.1
PROC_PWR_EN31: IN31.1, OUT31.1
PROC_PWR_EN32: IN32.1, OUT32.1
PROC_PWR_EN33: IN33.1, OUT33.1
PROC_PWR_EN34: IN34.1, OUT34.1
PROC_PWR_EN35: IN35.1, OUT35.1
PROC_PWR_EN36: IN36.1, OUT36.1
PROC_PWR_EN37: IN37.1, OUT37.1
PROC_PWR_EN38: IN38.1, OUT38.1
PROC_PWR_EN39: IN39.1, OUT39.1
PROC_PWR_EN40: IN40.1, OUT40.1
PROC_PWR_EN41: IN41.1, OUT41.1
PROC_PWR_EN42: IN42.1, OUT42.1
PROC_PWR_EN43: IN43.1, OUT43.1
PROC_PWR_EN44: IN44.1, OUT44.1
PROC_PWR_EN45: IN45.1, OUT45.1
PROC_PWR_EN46: IN46.1, OUT46.1
PROC_PWR_EN47: IN47.1, OUT47.1
SCL: IN.13, OUT.13, R3.1, U1.6, U2.4, U3.1
SCL1: IN1.13, OUT1.13, R7.1, U4.6, U5.4, U6.1
SCL2: IN2.13, OUT2.13, R11.1, U7.6, U8.4, U9.1
SCL3: IN3.13, OUT3.13, R15.1, U10.6, U11.4, U12.1
SCL4: IN4.13, OUT4.13, R19.1, U13.6, U14.4, U15.1
SCL5: IN5.13, OUT5.13, R23.1, U16.6, U17.4, U18.1
SCL6: IN6.13, OUT6.13, R27.1, U19.6, U20.4, U21.1
SCL7: IN7.13, OUT7.13, R31.1, U22.6, U23.4, U24.1
SCL8: IN8.13, OUT8.13, R35.1, U25.6, U26.4, U27.1
SCL9: IN9.13, OUT9.13, R39.1, U28.6, U29.4, U30.1
SCL10: IN10.13, OUT10.13, R43.1, U31.6, U32.4, U33.1
SCL11: IN11.13, OUT11.13, R47.1, U34.6, U35.4, U36.1
SCL12: IN12.13, OUT12.13, R51.1, U37.6, U38.4, U39.1
SCL13: IN13.13, OUT13.13, R55.1, U40.6, U41.4, U42.1
SCL14: IN14.13, OUT14.13, R59.1, U43.6, U44.4, U45.1
SCL15: IN15.13, OUT15.13, R63.1, U46.6, U47.4, U48.1
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
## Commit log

2021-11-02 Add production files and README
2022-02-03 Add product image
